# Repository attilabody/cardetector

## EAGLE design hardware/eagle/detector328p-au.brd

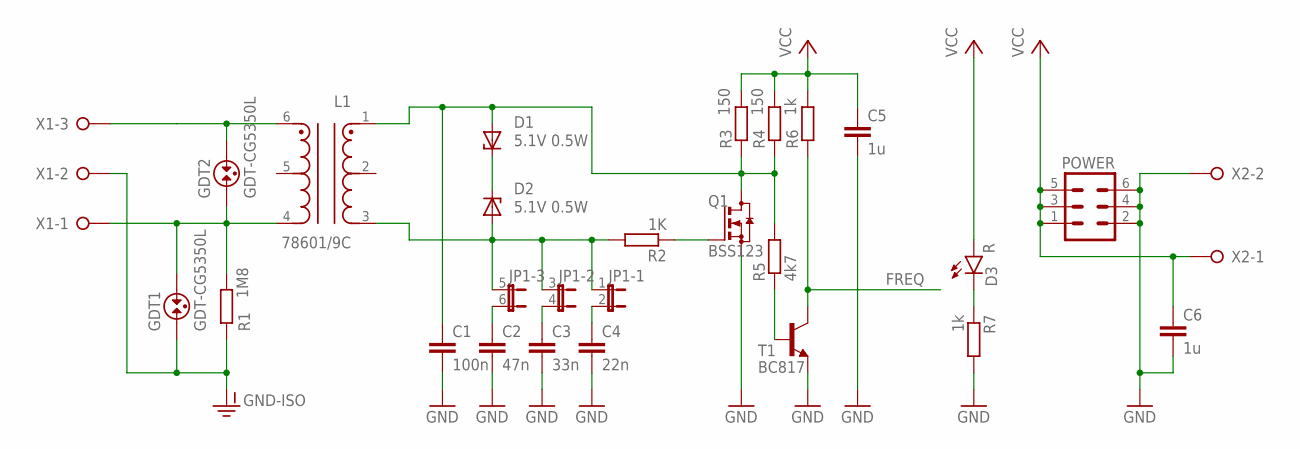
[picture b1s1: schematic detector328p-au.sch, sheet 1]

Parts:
C1: 100n; C0603
C2: 47n; C0603
C3: 33n; C0603
C4: 22n; C0603
C5, C6: 1u; C0603
D1, D2: 5.1V 0.5W; SOD80C
D3: R; LED-0603
GDT1, GDT2: GDT-CG5350L; CG5350L
JP1: JP3QE; JP3Q
L1: 78601/9C
POWER: MA03-2
Q1: BSS123; SOT23
R1: 1M8; R0603
R2: 1K; R0603
R3, R4: 150; R0603
R5: 4k7; R0603
R6, R7: 1k; R0603
T1: BC817; SOT23-BEC
X1: W237-3E
X2: W237-02P; W237-132

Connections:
FREQ: R6.1, T1.C; also elsewhere on the board
GND: C1.2, C2.2, C3.2, C4.2, C5.2, C6.2, POWER.2, POWER.4, POWER.6, Q1.2 (S), R7.2, T1.E, X2.2; also elsewhere on the board
GND-ISO: GDT1.1, R1.1, X1.2
unnamed: D1.C, D2.C
unnamed: R5.1, T1.B
unnamed: Q1.1 (G), R2.1
unnamed: C3.1, JP1.4 (2)
unnamed: C4.1, JP1.2
unnamed: D2.A, JP1.1, JP1.3 (1), JP1.5 (1), L1.3, R2.2
unnamed: GDT2.2, L1.6, X1.3
unnamed: C2.1, JP1.6 (2)
unnamed: C1.1, D1.A, L1.1, Q1.3 (D), R3.1, R4.1, R5.2
unnamed: GDT1.2, GDT2.1, L1.4, R1.2, X1.1
unnamed: D3.C, R7.1
VCC: C5.1, C6.1, D3.A, POWER.1, POWER.3, POWER.5, R3.2, R4.2, R6.2, X2.1; also elsewhere on the board

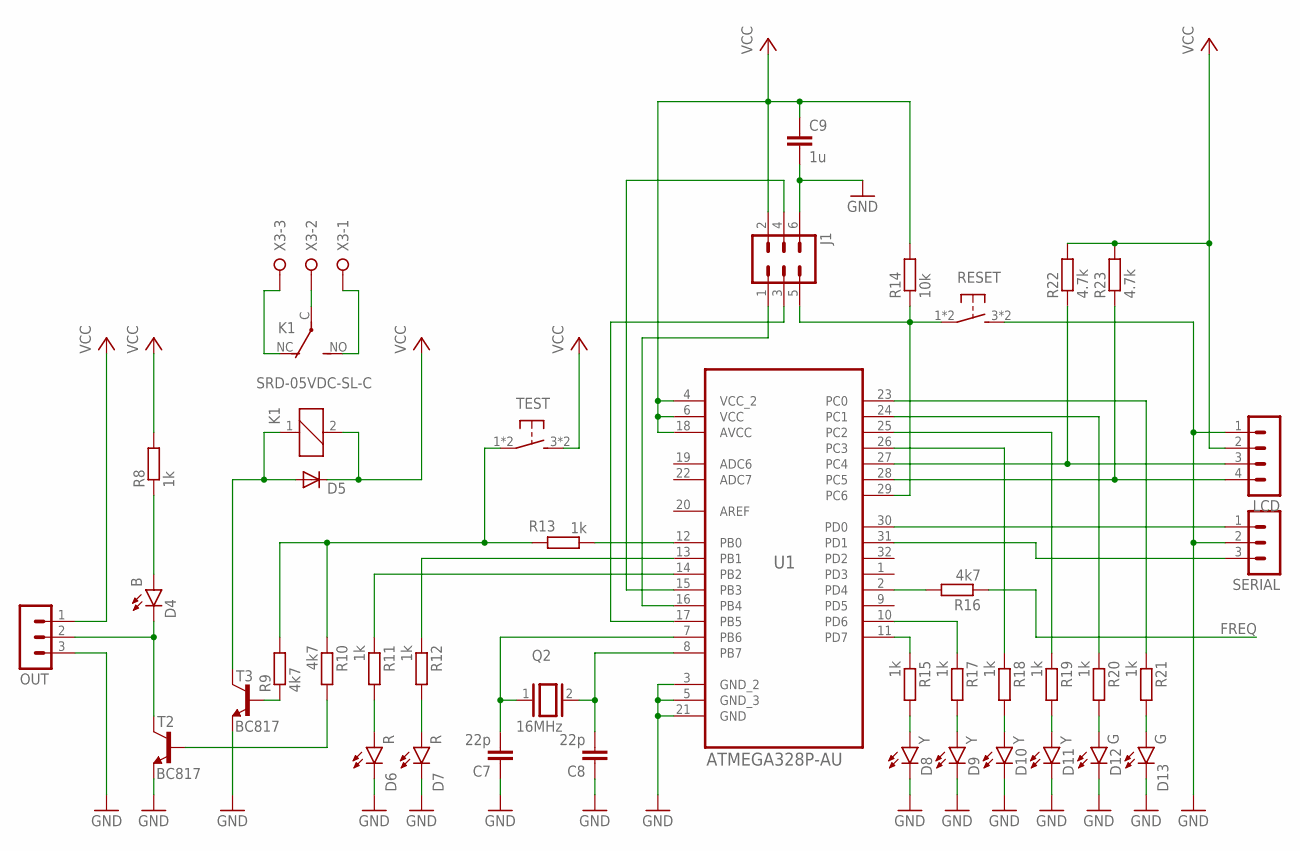
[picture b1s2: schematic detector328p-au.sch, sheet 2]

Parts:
C7, C8: 22p; C0603
C9: 1u; C0603
D4: B; LED-0603
D5: DIODE-SOD80C; SOD80C
D6, D7: R; LED-0603
D8, D9, D10, D11: Y; LED-0603
D12, D13: G; LED-0603
J1: MA03-2
K1: SRD-05VDC-SL-C; JS-M
LCD: MA04-1
OUT: MA03-1
Q2: 16MHz; QS
R8, R11, R12, R13, R15, R17, R18, R19, R20, R21: 1k; R0603
R9, R10, R16: 4k7; R0603
R14: 10k; R0603
R22, R23: 4.7k; R0603
RESET: 10-XX; B3F-10XX
SERIAL: MA03-1
T2, T3: BC817; SOT23-BEC
TEST: 10-XX; B3F-10XX
U1: ATMEGA328P-AU; QFP80P900X900X120-32N
X3: W237-3E

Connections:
FREQ: R16.1; also elsewhere on the board
GND: C7.1, C8.1, C9.2, D6.C, D7.C, D8.C, D9.C, D10.C, D11.C, D12.C, D13.C, J1.6, LCD.1, OUT.3, RESET.3 (S), RESET.4 (S), SERIAL.2, T2.E, T3.E, U1.3 (GND_2), U1.5 (GND_3), U1.21 (GND); also elsewhere on the board
unnamed: C7.2, Q2.1, U1.7 (PB6)
unnamed: R16.2, U1.2 (PD4)
unnamed: C8.2, Q2.2, U1.8 (PB7)
unnamed: J1.1, U1.16 (PB4)
unnamed: J1.4, U1.15 (PB3)
unnamed: J1.3, U1.17 (PB5)
unnamed: D9.A, R17.2
unnamed: D10.A, R18.2
unnamed: D11.A, R19.2
unnamed: D12.A, R20.2
unnamed: R10.2, T2.B
unnamed: D4.C, OUT.2, T2.C
unnamed: D4.A, R8.1
unnamed: R17.1, U1.10 (PD6)
unnamed: R15.1, U1.11 (PD7)
unnamed: D8.A, R15.2
unnamed: R18.1, U1.26 (PC3)
unnamed: R19.1, U1.25 (PC2)
unnamed: J1.5, R14.1, RESET.1, RESET.2, U1.29 (PC6)
unnamed: R20.1, U1.24 (PC1)
unnamed: D13.A, R21.2
unnamed: R21.1, U1.23 (PC0)
unnamed: D7.A, R12.2
unnamed: D6.A, R11.2
unnamed: R11.1, U1.14 (PB2)
unnamed: R12.1, U1.13 (PB1)
unnamed: D5.A, K1.1, T3.C
unnamed: SERIAL.1, U1.30 (PD0)
unnamed: R9.1, T3.B
unnamed: K1.NC (O), X3.3
unnamed: K1.NO (S), X3.1
unnamed: K1.C, X3.2
unnamed: LCD.4, R23.1, U1.28 (PC5)
unnamed: LCD.3, R22.1, U1.27 (PC4)
unnamed: R13.1, U1.12 (PB0)
unnamed: R9.2, R10.1, R13.2, TEST.1, TEST.2
unnamed: SERIAL.3, U1.31 (PD1)
VCC: C9.1, D5.C, J1.2, K1.2, LCD.2, OUT.1, R8.2, R14.2, R22.2, R23.2, TEST.3 (S), TEST.4 (S), U1.4 (VCC_2), U1.6 (VCC), U1.18 (AVCC); also elsewhere on the board

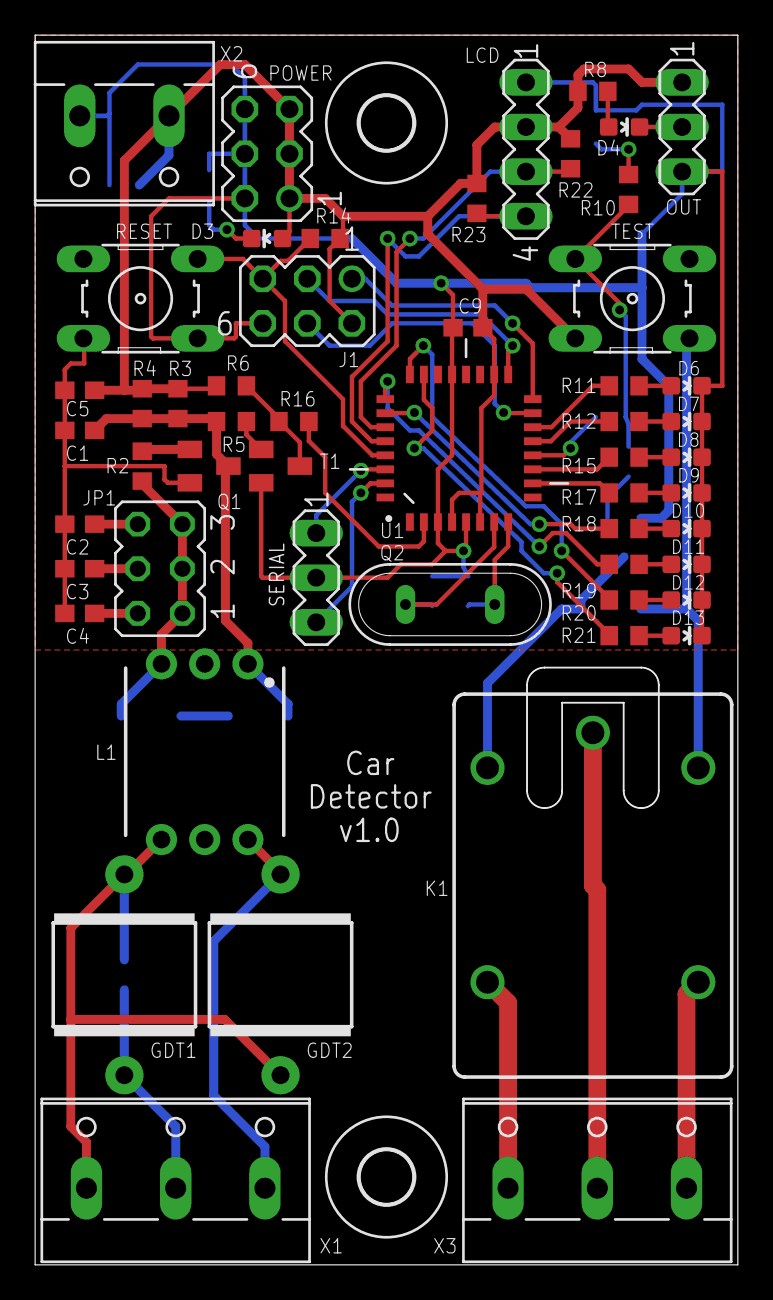
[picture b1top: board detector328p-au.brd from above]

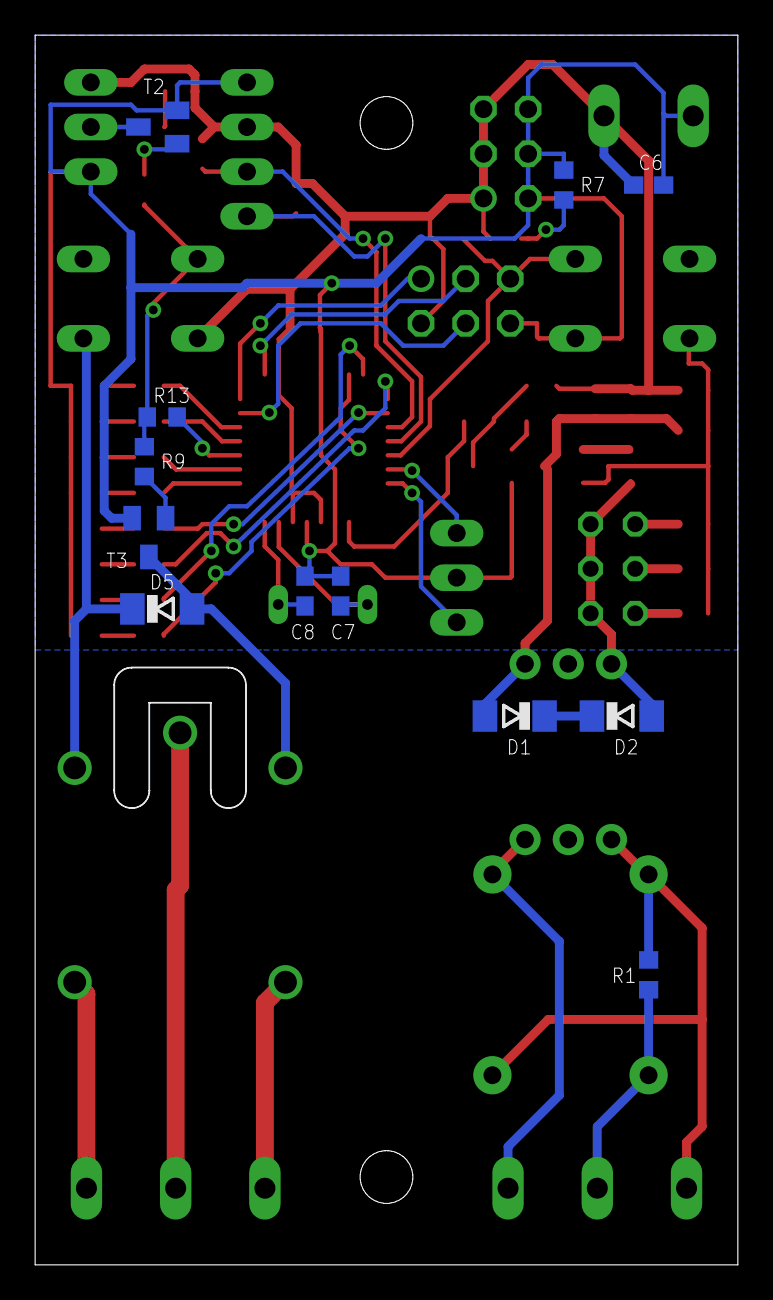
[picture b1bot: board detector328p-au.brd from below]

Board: 2 copper layers, 39.9 x 69.9 mm, 68 parts (12 on the bottom side), 52 nets.

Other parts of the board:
U$1, U$2: 3,0

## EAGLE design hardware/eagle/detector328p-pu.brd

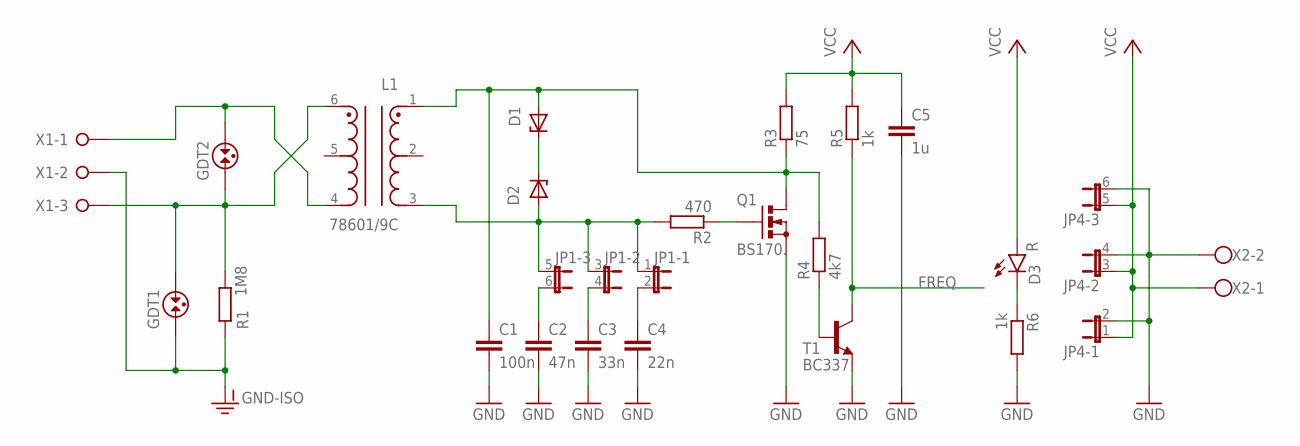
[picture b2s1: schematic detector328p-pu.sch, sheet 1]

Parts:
C1: 100n; C025-025X050
C2: 47n; C025-025X050
C3: 33n; C025-025X050
C4: 22n; C025-025X050
C5: 1u; C025-030X050
D1, D2: 24V; ZDIO-5
D3: R; LED3MM
GDT1, GDT2: GDT-CG5350L; CG5350L
JP1, JP4: JP3QE; JP3Q
L1: 78601/9C
Q1: BS170.; TO92-DGS
R1: 1M8; 0204/5
R2: 470; 0204/5
R3: 75; 0204/7
R4: 4k7; 0204/5
R5, R6: 1k; 0204/5
T1: BC337; TO92-CBE
X1: W237-03P; W237-133
X2: W237-102

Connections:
FREQ: R5.1, T1.C; also elsewhere on the board
GND: C1.2, C2.2, C3.2, C4.2, C5.2, JP4.2, JP4.4 (2), JP4.6 (2), Q1.S, R6.2, T1.E, X2.2; also elsewhere on the board
GND-ISO: GDT1.1, R1.1, X1.2
unnamed: D1.C, D2.C
unnamed: R4.1, T1.B
unnamed: Q1.G, R2.1
unnamed: C3.1, JP1.4 (2)
unnamed: C4.1, JP1.2
unnamed: D2.A, JP1.1, JP1.3 (1), JP1.5 (1), L1.3, R2.2
unnamed: GDT2.2, L1.4, X1.1
unnamed: C2.1, JP1.6 (2)
unnamed: C1.1, D1.A, L1.1, Q1.D, R3.1, R4.2
unnamed: D3.K (C), R6.1
unnamed: GDT1.2, GDT2.1, L1.6, R1.2, X1.3
VCC: C5.1, D3.A, JP4.1, JP4.3 (1), JP4.5 (1), R3.2, R5.2, X2.1; also elsewhere on the board

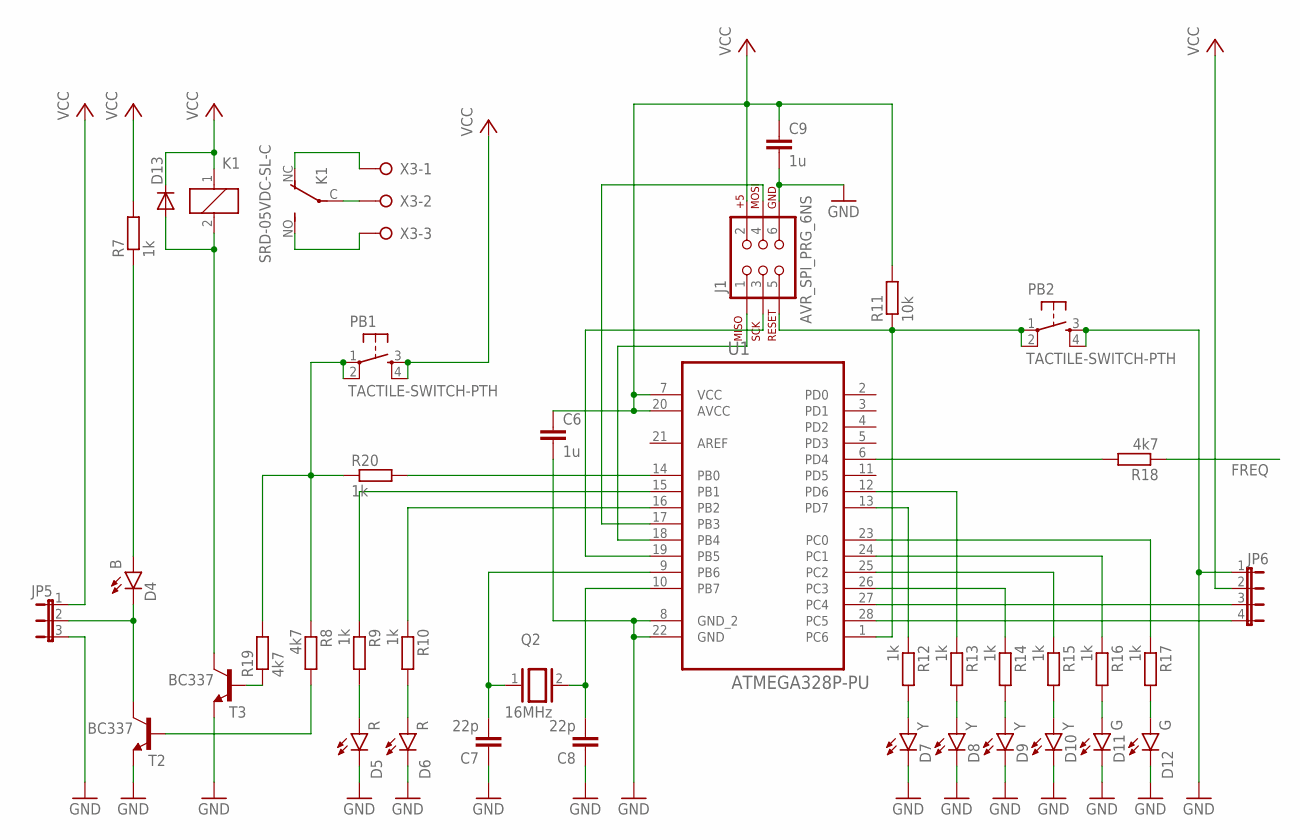
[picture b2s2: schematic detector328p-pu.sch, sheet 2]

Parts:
C6, C9: 1u; C025-030X050
C7, C8: 22p; C025-025X050
D4: B; LED3MM
D5, D6: R; LED3MM
D7, D8, D9, D10: Y; LED3MM
D11, D12: G; LED3MM
D13: DIODE-D-5; D-5
J1: AVR_SPI_PRG_6NS; 2X3-NS
JP5: JP2E; JP2
JP6: JP4E; JP4
K1: SRD-05VDC-SL-C; JS-M
PB1, PB2: TACTILE-SWITCH-PTH; TAC-SWITCH-PTH
Q2: 16MHz; QS
R7, R9, R10, R12, R13, R14, R15, R16, R17, R20: 1k; 0204/5
R8, R18, R19: 4k7; 0204/5
R11: 10k; 0204/5
T2, T3: BC337; TO92-CBE
U1: ATMEGA328P-PU; DIP254P762X457-28
X3: W237-03P; W237-133

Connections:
FREQ: R18.1; also elsewhere on the board
GND: C6.2, C7.1, C8.1, C9.2, D5.K (C), D6.K (C), D7.K (C), D8.K (C), D9.K (C), D10.K (C), D11.K (C), D12.K (C), J1.6, JP5.3, JP6.1, PB2.3, PB2.4, T2.E, T3.E, U1.8 (GND_2), U1.22 (GND); also elsewhere on the board
unnamed: C7.2, Q2.1, U1.9 (PB6)
unnamed: R18.2, U1.6 (PD4)
unnamed: C8.2, Q2.2, U1.10 (PB7)
unnamed: J1.1, U1.18 (PB4)
unnamed: J1.4, U1.17 (PB3)
unnamed: J1.3, U1.19 (PB5)
unnamed: D8.A, R13.2
unnamed: D9.A, R14.2
unnamed: D10.A, R15.2
unnamed: D11.A, R16.2
unnamed: R8.2, T2.B
unnamed: R20.2, U1.14 (PB0)
unnamed: D4.K (C), JP5.2, T2.C
unnamed: D4.A, R7.1
unnamed: R13.1, U1.12 (PD6)
unnamed: R12.1, U1.13 (PD7)
unnamed: D7.A, R12.2
unnamed: R14.1, U1.26 (PC3)
unnamed: R15.1, U1.25 (PC2)
unnamed: JP6.4, U1.28 (PC5)
unnamed: R16.1, U1.24 (PC1)
unnamed: D12.A, R17.2
unnamed: R17.1, U1.23 (PC0)
unnamed: D6.A, R10.2
unnamed: D5.A, R9.2
unnamed: R10.1, U1.16 (PB2)
unnamed: R9.1, U1.15 (PB1)
unnamed: PB1.1, PB1.2, R8.1, R19.2, R20.1
unnamed: D13.A, K1.2, T3.C
unnamed: R19.1, T3.B
unnamed: K1.NC (O), X3.1
unnamed: K1.NO (S), X3.3
unnamed: K1.C, X3.2
unnamed: J1.5, PB2.1, PB2.2, R11.1, U1.1 (PC6)
unnamed: JP6.3, U1.27 (PC4)
VCC: C6.1, C9.1, D13.C, J1.2, JP5.1, JP6.2, K1.1, PB1.3, PB1.4, R7.2, R11.2, U1.7 (VCC), U1.20 (AVCC); also elsewhere on the board

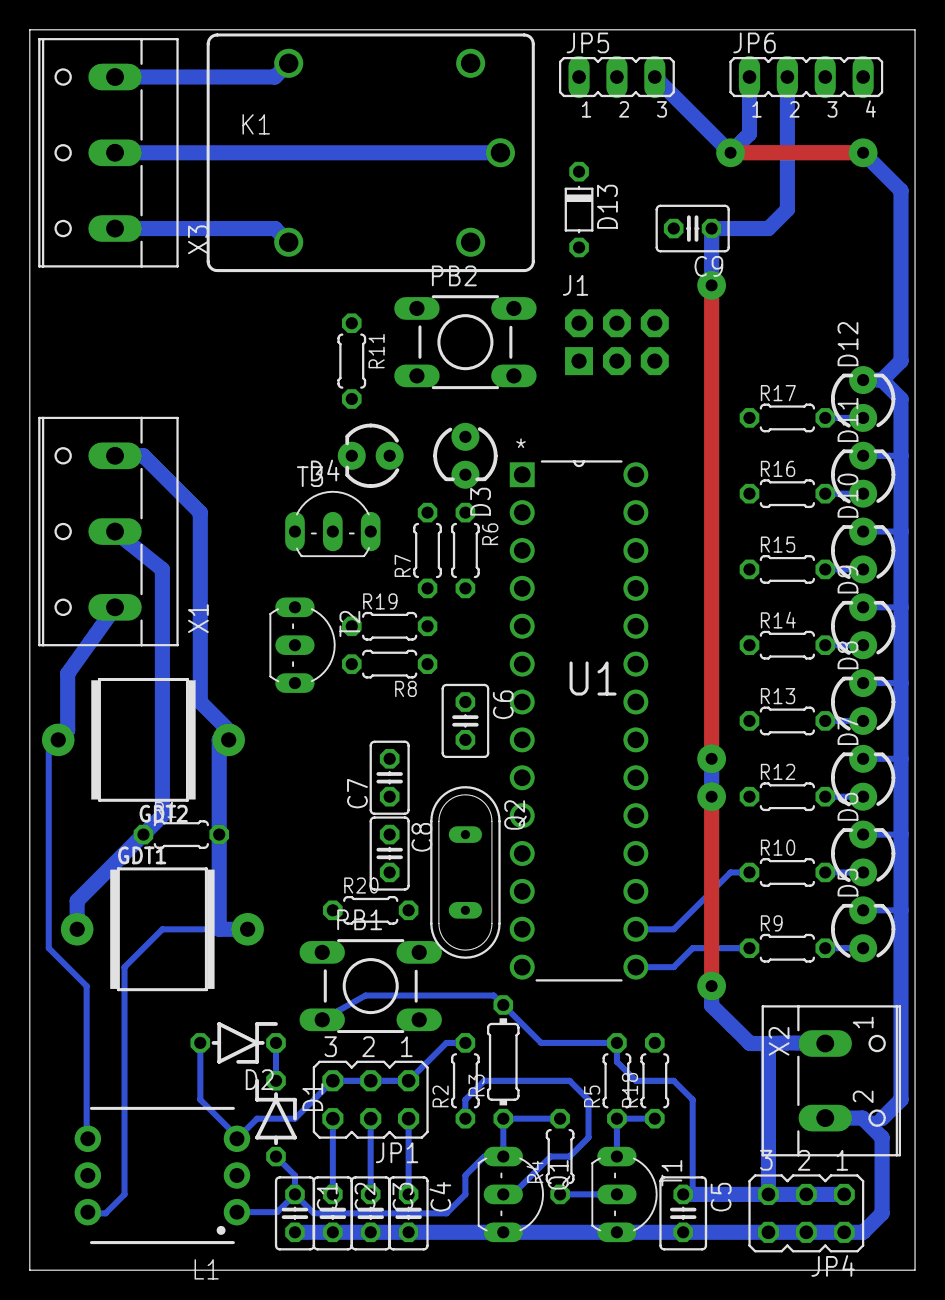
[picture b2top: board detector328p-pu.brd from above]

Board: 2 copper layers, 59.4 x 83.2 mm, 62 parts (0 on the bottom side), 50 nets.

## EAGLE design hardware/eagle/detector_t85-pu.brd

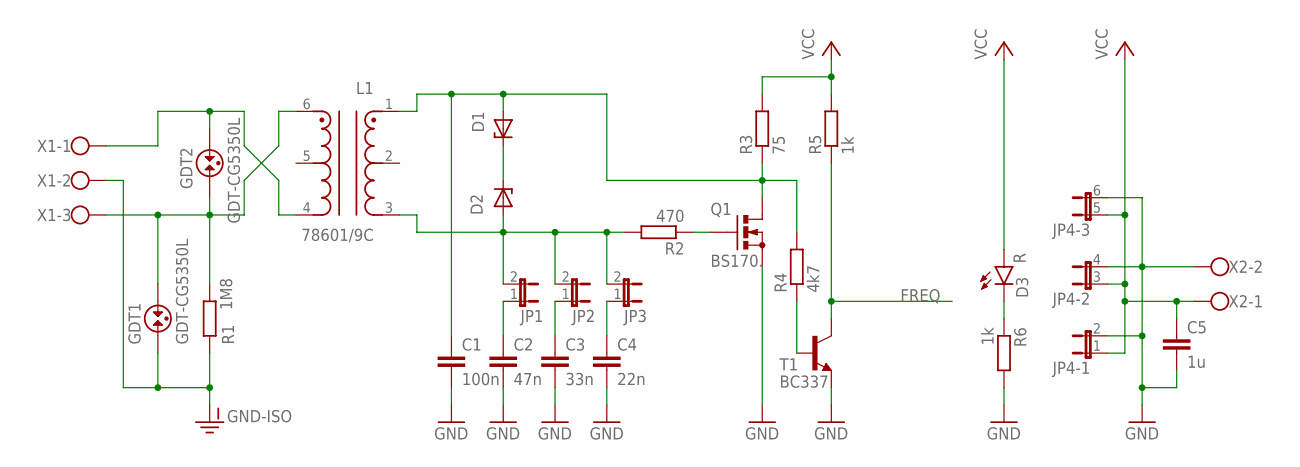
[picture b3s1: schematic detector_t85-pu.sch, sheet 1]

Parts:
C1: 100n; C050-024X044
C2: 47n; C050-024X044
C3: 33n; C050-024X044
C4: 22n; C050-024X044
C5: 1u; C050-025X075
D1, D2: 24V; ZDIO-5
D3: R; LED3MM
GDT1, GDT2: GDT-CG5350L; CG5350L
JP1, JP2, JP3: JUMPER-2PTH; 1X02
JP4: JP3QE; JP3Q
L1: 78601/9C
Q1: BS170.; TO92-DGS
R1: 1M8; 0204/5
R2: 470; 0204/5
R3: 75; 0204/7
R4: 4k7; 0204/5
R5, R6: 1k; 0204/5
T1: BC337; TO92-CBE
X1: W237-103
X2: W237-102

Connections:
FREQ: R5.1, T1.C; also elsewhere on the board
GND: C1.2, C2.2, C3.2, C4.2, C5.2, JP4.2, JP4.4 (2), JP4.6 (2), Q1.S, R6.2, T1.E, X2.2; also elsewhere on the board
GND-ISO: GDT1.1, R1.1, X1.2
unnamed: D1.C, D2.C
unnamed: R4.1, T1.B
unnamed: Q1.G, R2.1
unnamed: C3.1, JP2.1
unnamed: C4.1, JP3.1
unnamed: D2.A, JP1.2, JP2.2, JP3.2, L1.3, R2.2
unnamed: GDT2.2, L1.4, X1.1
unnamed: C2.1, JP1.1
unnamed: C1.1, D1.A, L1.1, Q1.D, R3.1, R4.2
unnamed: GDT1.2, GDT2.1, L1.6, R1.2, X1.3
unnamed: D3.K (C), R6.1
VCC: C5.1, D3.A, JP4.1, JP4.3 (1), JP4.5 (1), R3.2, R5.2, X2.1; also elsewhere on the board

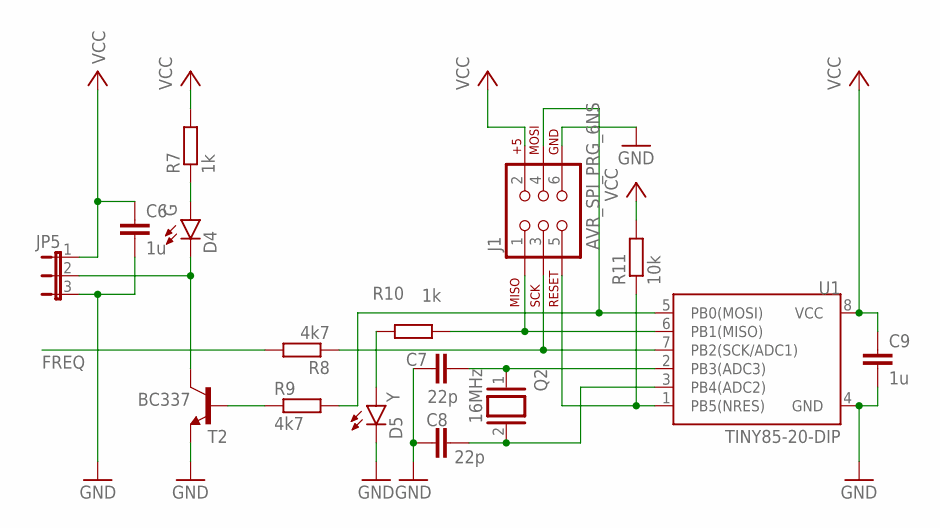
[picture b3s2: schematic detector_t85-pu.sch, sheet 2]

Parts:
C6, C9: 1u; C050-025X075
C7, C8: 22p; CAP-PTH-SMALL2
D4: G; LED3MM
D5: Y; LED3MM
J1: AVR_SPI_PRG_6NS; 2X3-NS
JP5: JP2E; JP2
Q2: 16MHz; QS
R7, R10: 1k; 0204/5
R8, R9: 4k7; 0204/5
R11: 10k; 0204/5
T2: BC337; TO92-CBE
U1: TINY85-20-DIP; DIP08

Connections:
FREQ: R8.2; also elsewhere on the board
GND: C6.2, C7.1, C8.1, C9.2, D5.K (C), J1.6, JP5.3, T2.E, U1.4 (GND); also elsewhere on the board
unnamed: R9.1, T2.B
unnamed: D4.K (C), JP5.2, T2.C
unnamed: D4.A, R7.1
unnamed: C7.2, Q2.1, U1.2 (PB3(ADC3))
unnamed: C8.2, Q2.2, U1.3 (PB4(ADC2))
unnamed: D5.A, R10.2
unnamed: J1.1, R10.1, U1.6 (PB1(MISO))
unnamed: J1.4, R9.2, U1.5 (PB0(MOSI))
unnamed: J1.5, R11.1, U1.1 (PB5(NRES))
unnamed: J1.3, R8.1, U1.7 (PB2(SCK/ADC1))
VCC: C6.1, C9.1, J1.2, JP5.1, R7.2, R11.2, U1.8 (VCC); also elsewhere on the board

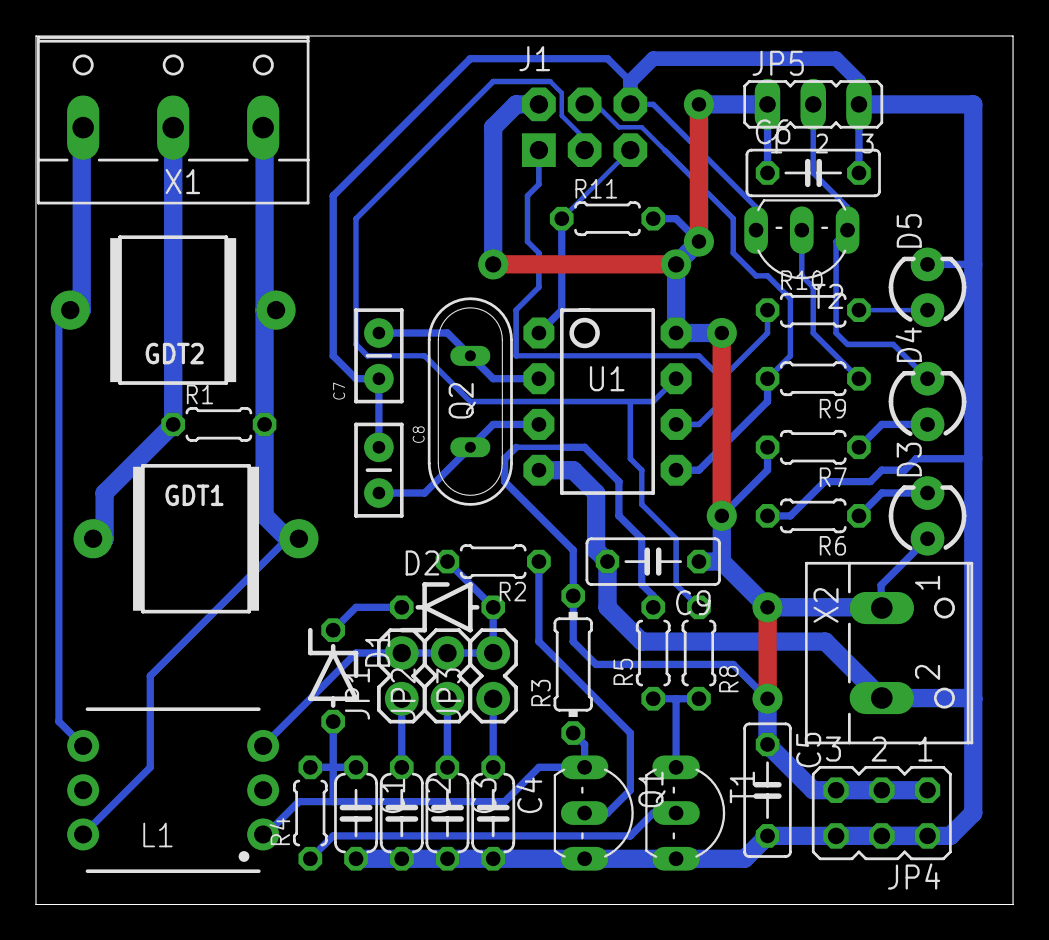
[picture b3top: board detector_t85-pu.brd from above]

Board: 2 copper layers, 54.3 x 48.2 mm, 41 parts (0 on the bottom side), 25 nets.

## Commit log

2016-04-29 cardetector: initial commit
2016-05-14 serial output for debugging
2016-05-14 using timer0 instead of timer1
2016-05-14 continous counter opeartion
2016-05-14 average
2016-05-14 first it-may-even-work version
2016-05-16 serial code embedded only when absolutely necessary; params struct, function provided to read them from eeprom timelimit interpreted in seconds (4 samples) instead of samples
2016-05-18 Pins and timers selected in config.h (cardetector.c became model independent) Separate pin for signaling and LED
2016-05-22 Rejoining 328p and tiny85 code
2016-05-26 detection fine-tuning
2016-05-29 detector shamatics added
2016-05-29 hardware: replaced impulse transformer, VCC capacitors added
2016-05-29 fixing TIFR T0 overflow interrupt pending bit reset (0->1)
2016-06-02 adding bidirectional diff shift feature (right shift on negative values)
2016-06-02 hardware: separate pages for analog and digital part, separate schematics for tiny85 and mega328p
2016-06-02 hardware: t85 board fuckery
2016-06-02 hardware: t85 all parts on the board
2016-06-02 hardware-t85: almost there
2016-06-02 hardware: separate DIP and SIL drawings for mega328p, gitignore tuning
2016-06-02 hardware: renamed schs to reflect the CPU (variant) used.
2016-06-03 hardware-t85: really almost there
2016-06-04 hardware-m328p-au: preparing schematics for board creation
2016-06-05 hardware-m328p-pu: board created
2016-06-05 hardware-m328p-au: MCU referred from gate433.lbr
2016-06-05 hardware-328p-au: more smt replacements
2016-06-08 Board level 0
2016-06-10 detector328p-au level 1: devices at place
2016-06-11 detector328p-au almost wired
2016-06-11 detector328p-au wiring ready, labels need fixing
2016-06-11 detector328p-au final
2016-06-11 detector328p-au serial port
2016-06-11 detector328p-au R2->1K, T1->BC817
2016-06-12 hardware: eagle files moved from hardware/ to hardware/eagle/ .gitignore prepared for kicad files
2016-06-13 detector_t85-pu: T2 10K pull-up, Zener 5,1V -> 20V
2016-06-13 hardware/kicad/328p-au: schematic created
2016-06-13 hardware/kicad/328p-au: separated output sheet
2016-06-14 hardware/kicad/328p-au: separated collpits page, footprints assigned and imported to PCB
2016-06-19 hardware/kicad/328p-au: use 3x2 jumper block for frequency selection
2016-06-19 cardetector: i2c handler, dead code elimination
2016-06-20 cardetector: PCF8574 I/O extender
2016-06-22 cardetector: i2c LCD
2016-06-24 hardware/eagle: added 3 push buttons
2016-06-24 hardware/kicad: added serial connector && 3 push buttons
2016-06-24 CarDetector v1.1 hardware (3 more button)
2016-06-25 Interrupt driven serial communication proto
2016-06-25 atmel studio project files
2016-06-27 serial commands
2016-06-28 serial command: show
2016-07-01 cardetector: parameter tuning over serial console
2016-07-02 cardetector: parallel build, serial code #ifdefs
2016-07-04 Fix: detector_t85-pu: T2 10K pull-up, Zener 5,1V -> 20V
2016-07-10 cardetector: refactoring, led bar implementation
2016-07-13 cardetector: serial debug on/of
2016-07-15 cardetector: added Makefile
2016-07-23 C1: 1206; C2,C3,C4: 0805; Power polarity signs
2016-07-24 cardetector: WDT
2017-01-22 Atmel firmware moved to subfolder
2017-01-22 added stm32 firmware
2017-01-23 hardware/kicad/stm32f030: created
2017-01-24 hardware/kicad/stm32f030: progress
2017-01-28 hardware/kicad/stm32f030: modules ready
2017-01-30 stm32 debugger config
2017-01-31 slight;y modified module layout
2017-01-31 more optimizations on modules
2017-01-31 space for mounting hole
2017-02-02 PCB V0.90
2017-02-02 hardware/kicad: all LED IDs moved to the board area and made visible
2017-02-09 hardware/kicad/stm32f030: adding eeprom step1
2017-02-09 hardware/kicad/stm32f030: adding eeprom step2
2017-02-10 hardware/kicad/stm32f030: adding eeprom step3
2017-02-13 hardware/kicad/stm32f030: final touches
2017-02-14 hardware/kicad/stm32f030: i2c eeprom pad widening
2017-02-14 firmware/stm32: moved component initialization codes to separate c/h files
2017-02-14 firmware/stm32 f030f4Px firmware code moved to separate subfolder
2017-02-14 hardware/kicad/stm32f030: use upper layer zones for power
2017-02-15 hardware/kicad: cardetector.pretty moved from stm32f030 to ..
2017-02-15 hardware/kicad: stm32f103 created (stm32f030 copy)
2017-02-19 hardware/kicad/stm32f103: MCU/LED block ready
2017-02-21 hardware/kicad/stm32f103: Almost there...
2017-02-23 hardware/kicad/stm32f103: Minor cosmetic changes
2017-02-23 hardware/kicad/stm32f030: Ledbar removed, reorg started
2017-02-25 hardware/kicad/stm32f030: blocks ready
2017-02-28 hardware/kicad/stm32f030: everything is connected, DRC OK
2017-03-01 hardware/kicad/stm32f030: removed derecated libraries
2017-03-01 firmware/stm32/F103C8Tx firmware added
2017-03-05 firmware/stm32: renamed 103 and 030 projects
2017-03-05 firmware/stm32: i2cmaster, pcf8574, i2clcd added to cardetector_common
2017-03-05 hardware/kicad/stm32f030: changed i2c bus and eeprom voltage to 5V
2017-03-05 firmware/stm32/f030f4px: i2clcd and usart send test
2017-03-11 firmware/stm32/f030f4px: detection working
2017-03-12 firmware/stm32/cardetector_common fixes and improvements
2017-03-12 firmware/stm32 cardetector_common renamed to stm32plus, i2cmaster modularized i2ceeprom seems to work
2017-03-14 firmware/stm32/stm32plus: removed m_ prefixes, optimized i2clcd init
2017-03-17 firmware/stm32/F030F4Px Almost feature complete (only MCP23017 led bar missing, pcf8574 led bar untested)
2017-09-22 firmware/stm32/F030F4Px migrated to new cube && sw4stm32 versions iwdg switched on (code still should be written to work)
2017-09-22 firmware/stm32/F030F4Px: fine-tuning USE_ flag usage
2017-09-22 hardware/kicad/stm32f030: kicad version && lib bump
2017-09-27 stm32f030 PCB text fixes
2017-09-28 Atmel firmware serial buffer size (theoretical) bug fix
2017-10-01 st: various minor fixes
2017-10-02 barechip-F030F4Px added (board test)
2017-10-03 Removing accidentally added backup files
2017-10-03 kicad/stm32f030: corrected board size
2017-10-06 ST firmware usart library changes
2017-10-06 firmware/stm32/barechip-F030F4Px chagnes
2017-10-06 STM32F030F4Px firmware adoption to proto board implementation
2017-10-08 Made lcd/ledbar mutually exclusive again (too much effort to make them work parallel and would not fit to 030f4
2017-10-08 ledbar values from config
2017-10-23 STM32f030F4Px V0.99
2017-10-23 kicad-STM32F030 modifications during test batch assembly
2017-12-05 checked in last state of firmware/stm32/barechip test project
2018-01-26 stm32plus: extern "C" into the headers for mixed projects
2018-01-26 STM32F030F4Px: copied Drivrers/uart.c into Application folder to protect from overwriting by CubeMX
2018-04-12 Added licecse
2019-07-16 Making to compile with newer SW4STM32 version
2019-07-20 Rebuilt project structure

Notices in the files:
parts and their libraries:
SparkFun-LED: Licensing: Creative Commons ShareAlike 4.0 International - https://creativecommons.org/licenses/by-sa/4.0
supressor: Copyright (C) 2009, Bob Starr
